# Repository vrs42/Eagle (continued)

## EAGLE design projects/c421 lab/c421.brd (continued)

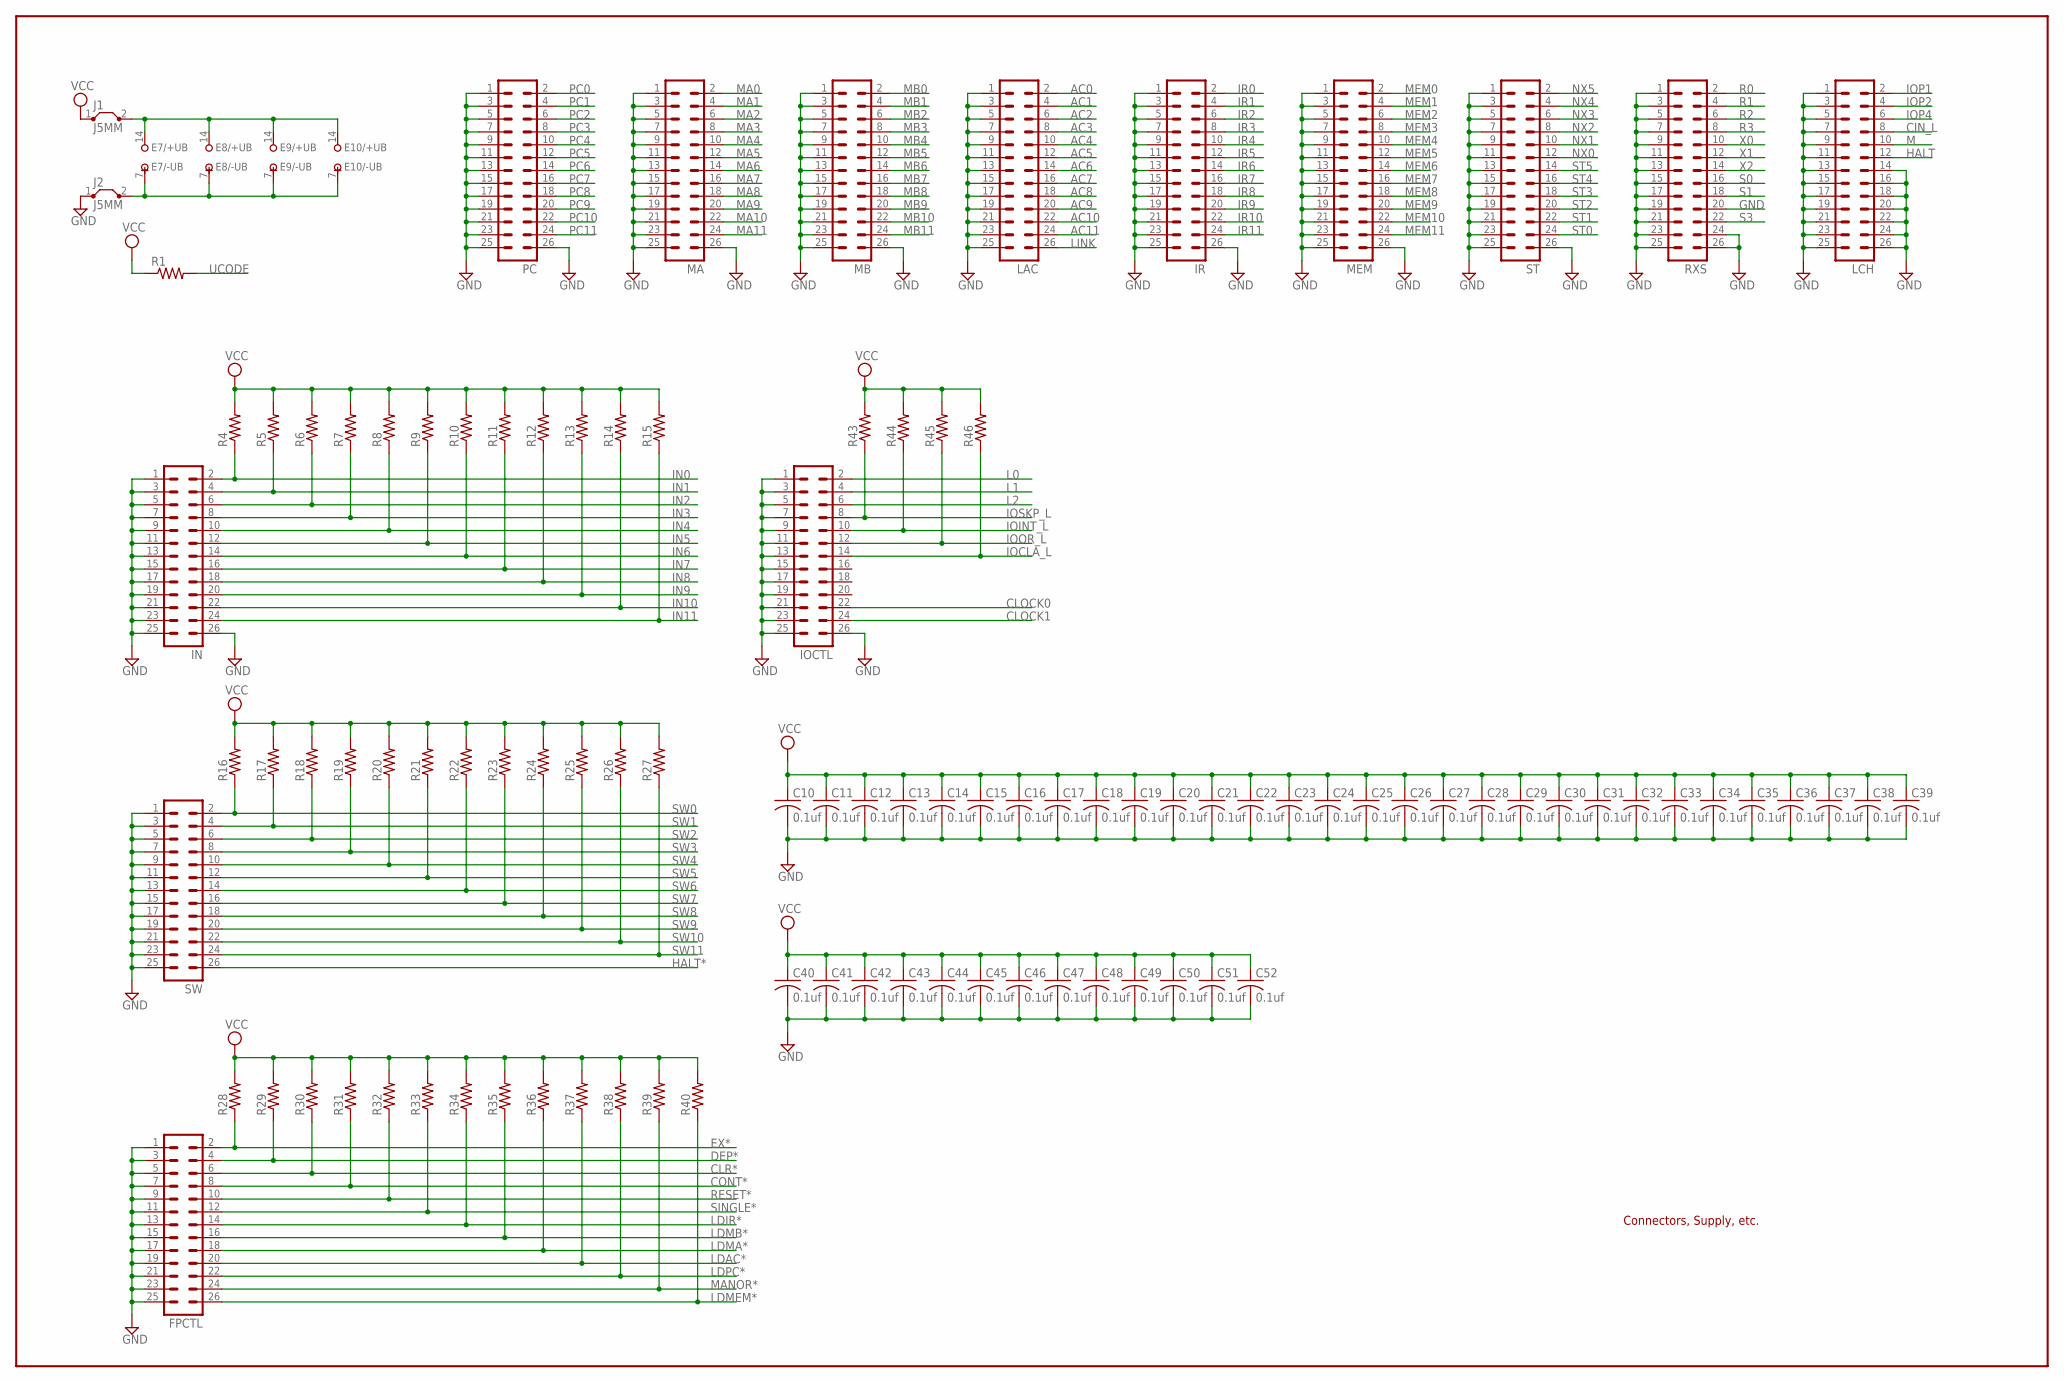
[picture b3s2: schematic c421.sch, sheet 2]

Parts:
C10, C11, C12, C13, C14, C15, C16, C17, C18, C19, C20, C21, C22, C23, C24, C25, C26, C27, C28, C29, C30, C31, C32, C33, C34, C35, C36, C37, C38, C39, C40, C41, C42, C43, C44, C45, C46, C47, C48, C49, C50, C51, C52: 0.1uf; C050-025X075
E7, E8, E9, E10: 744078N; DIL14
FPCTL: ML26
IN: ML26
IOCTL: ML26
IR: ML26
J1, J2: J5MM; 05
LAC: ML26
LCH: ML26
MA: ML26
MB: ML26
MEM: ML26
PC: ML26
R1, R4, R5, R6, R7, R8, R9, R10, R11, R12, R13, R14, R15, R16, R17, R18, R19, R20, R21, R22, R23, R24, R25, R26, R27, R28, R29, R30, R31, R32, R33, R34, R35, R36, R37, R38, R39, R40, R43, R44, R45, R46: R-US_0207/10; 0207/10
RXS: ML26
ST: ML26
SW: ML26

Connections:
+UB: E7.14 (+UB), E8.14 (+UB), E9.14 (+UB), E10.14 (+UB), J1.2
-UB: E7.7 (-UB), E8.7 (-UB), E9.7 (-UB), E10.7 (-UB), J2.2
AC0: LAC.2; also elsewhere on the board
AC1: LAC.4; also elsewhere on the board
AC2: LAC.6; also elsewhere on the board
AC3: LAC.8; also elsewhere on the board
AC4: LAC.10; also elsewhere on the board
AC5: LAC.12; also elsewhere on the board
AC6: LAC.14; also elsewhere on the board
AC7: LAC.16; also elsewhere on the board
AC8: LAC.18; also elsewhere on the board
AC9: LAC.20; also elsewhere on the board
AC10: LAC.22; also elsewhere on the board
AC11: LAC.24; also elsewhere on the board
CIN_L: LCH.8; also elsewhere on the board
CLOCK0: IOCTL.22; also elsewhere on the board
CLOCK1: IOCTL.24; also elsewhere on the board
CLR*: FPCTL.6, R30.1; also elsewhere on the board
CONT*: FPCTL.8, R31.1; also elsewhere on the board
DEP*: FPCTL.4, R29.1; also elsewhere on the board
EX*: FPCTL.2, R28.1; also elsewhere on the board
GND: C10.2, C11.2, C12.2, C13.2, C14.2, C15.2, C16.2, C17.2, C18.2, C19.2, C20.2, C21.2, C22.2, C23.2, C24.2, C25.2, C26.2, C27.2, C28.2, C29.2, C30.2, C31.2, C32.2, C33.2, C34.2, C35.2, C36.2, C37.2, C38.2, C39.2, C40.2, C41.2, C42.2, C43.2, C44.2, C45.2, C46.2, C47.2, C48.2, C49.2, C50.2, C51.2, C52.2, FPCTL.1, FPCTL.3, FPCTL.5, FPCTL.7, FPCTL.9, FPCTL.11, FPCTL.13, FPCTL.15, FPCTL.17, FPCTL.19, FPCTL.21, FPCTL.23, FPCTL.25, IN.1, IN.3, IN.5, IN.7, IN.9, IN.11, IN.13, IN.15, IN.17, IN.19, IN.21, IN.23, IN.25, IN.26, IOCTL.1, IOCTL.3, IOCTL.5, IOCTL.7, IOCTL.9, IOCTL.11, IOCTL.13, IOCTL.15, IOCTL.17, IOCTL.19, IOCTL.21, IOCTL.23, IOCTL.25, IOCTL.26, IR.1, IR.3, IR.5, IR.7, IR.9, IR.11, IR.13, IR.15, IR.17, IR.19, IR.21, IR.23, IR.25, IR.26, J2.1, LAC.1, LAC.3, LAC.5, LAC.7, LAC.9, LAC.11, LAC.13, LAC.15, LAC.17, LAC.19, LAC.21, LAC.23, LAC.25, LCH.1, LCH.3, LCH.5, LCH.7, LCH.9, LCH.11, LCH.13, LCH.14, LCH.15, LCH.16, LCH.17, LCH.18, LCH.19, LCH.20, LCH.21, LCH.22, LCH.23, LCH.24, LCH.25, LCH.26, MA.1, MA.3, MA.5, MA.7, MA.9, MA.11, MA.13, MA.15, MA.17, MA.19, MA.21, MA.23, MA.25, MA.26, MB.1, MB.3, MB.5, MB.7, MB.9, MB.11, MB.13, MB.15, MB.17, MB.19, MB.21, MB.23, MB.25, MB.26, MEM.1, MEM.3, MEM.5, MEM.7, MEM.9, MEM.11, MEM.13, MEM.15, MEM.17, MEM.19, MEM.21, MEM.23, MEM.25, MEM.26, PC.1, PC.3, PC.5, PC.7, PC.9, PC.11, PC.13, PC.15, PC.17, PC.19, PC.21, PC.23, PC.25, PC.26, RXS.1, RXS.3, RXS.5, RXS.7, RXS.9, RXS.11, RXS.13, RXS.15, RXS.17, RXS.19, RXS.20, RXS.21, RXS.23, RXS.24, RXS.25, RXS.26, ST.1, ST.3, ST.5, ST.7, ST.9, ST.11, ST.13, ST.15, ST.17, ST.19, ST.21, ST.23, ST.25, ST.26, SW.1, SW.3, SW.5, SW.7, SW.9, SW.11, SW.13, SW.15, SW.17, SW.19, SW.21, SW.23, SW.25; also elsewhere on the board
HALT: LCH.12; also elsewhere on the board
HALT*: SW.26; also elsewhere on the board
IN0: IN.2, R4.1; also elsewhere on the board
IN1: IN.4, R5.1; also elsewhere on the board
IN2: IN.6, R6.1; also elsewhere on the board
IN3: IN.8, R7.1; also elsewhere on the board
IN4: IN.10, R8.1; also elsewhere on the board
IN5: IN.12, R9.1; also elsewhere on the board
IN6: IN.14, R10.1; also elsewhere on the board
IN7: IN.16, R11.1; also elsewhere on the board
IN8: IN.18, R12.1; also elsewhere on the board
IN9: IN.20, R13.1; also elsewhere on the board
IN10: IN.22, R14.1; also elsewhere on the board
IN11: IN.24, R15.1; also elsewhere on the board
IOCLA_L: IOCTL.14, R46.1; also elsewhere on the board
IOINT_L: IOCTL.10, R44.1; also elsewhere on the board
IOOR_L: IOCTL.12, R45.1; also elsewhere on the board
IOP1: LCH.2; also elsewhere on the board
IOP2: LCH.4; also elsewhere on the board
IOP4: LCH.6; also elsewhere on the board
IOSKP_L: IOCTL.8, R43.1; also elsewhere on the board
IR0: IR.2; also elsewhere on the board
IR1: IR.4; also elsewhere on the board
IR2: IR.6; also elsewhere on the board
IR3: IR.8; also elsewhere on the board
IR4: IR.10; also elsewhere on the board
IR5: IR.12; also elsewhere on the board
IR6: IR.14; also elsewhere on the board
IR7: IR.16; also elsewhere on the board
IR8: IR.18; also elsewhere on the board
IR9: IR.20; also elsewhere on the board
IR10: IR.22; also elsewhere on the board
IR11: IR.24; also elsewhere on the board
L0: IOCTL.2; also elsewhere on the board
L1: IOCTL.4; also elsewhere on the board
L2: IOCTL.6; also elsewhere on the board
LDAC*: FPCTL.20, R37.1; also elsewhere on the board
LDIR*: FPCTL.14, R34.1; also elsewhere on the board
LDMA*: FPCTL.18, R36.1; also elsewhere on the board
LDMB*: FPCTL.16, R35.1; also elsewhere on the board
LDMEM*: FPCTL.26, R40.1; also elsewhere on the board
LDPC*: FPCTL.22, R38.1; also elsewhere on the board
LINK: LAC.26; also elsewhere on the board
M: LCH.10; also elsewhere on the board
MA0: MA.2; also elsewhere on the board
MA1: MA.4; also elsewhere on the board
MA2: MA.6; also elsewhere on the board
MA3: MA.8; also elsewhere on the board
MA4: MA.10; also elsewhere on the board
MA5: MA.12; also elsewhere on the board
MA6: MA.14; also elsewhere on the board
MA7: MA.16; also elsewhere on the board
MA8: MA.18; also elsewhere on the board
MA9: MA.20; also elsewhere on the board
MA10: MA.22; also elsewhere on the board
MA11: MA.24; also elsewhere on the board
MANOR*: FPCTL.24, R39.1; also elsewhere on the board
MB0: MB.2; also elsewhere on the board
MB1: MB.4; also elsewhere on the board
MB2: MB.6; also elsewhere on the board
MB3: MB.8; also elsewhere on the board
MB4: MB.10; also elsewhere on the board
MB5: MB.12; also elsewhere on the board
MB6: MB.14; also elsewhere on the board
MB7: MB.16; also elsewhere on the board
MB8: MB.18; also elsewhere on the board
MB9: MB.20; also elsewhere on the board
MB10: MB.22; also elsewhere on the board
MB11: MB.24; also elsewhere on the board
MEM0: MEM.2; also elsewhere on the board
MEM1: MEM.4; also elsewhere on the board
MEM2: MEM.6; also elsewhere on the board
MEM3: MEM.8; also elsewhere on the board
MEM4: MEM.10; also elsewhere on the board
MEM5: MEM.12; also elsewhere on the board
MEM6: MEM.14; also elsewhere on the board
MEM7: MEM.16; also elsewhere on the board
MEM8: MEM.18; also elsewhere on the board
MEM9: MEM.20; also elsewhere on the board
MEM10: MEM.22; also elsewhere on the board
MEM11: MEM.24; also elsewhere on the board
NX0: ST.12; also elsewhere on the board
NX1: ST.10; also elsewhere on the board
NX2: ST.8; also elsewhere on the board
NX3: ST.6; also elsewhere on the board
NX4: ST.4; also elsewhere on the board
NX5: ST.2; also elsewhere on the board
PC0: PC.2; also elsewhere on the board
PC1: PC.4; also elsewhere on the board
PC2: PC.6; also elsewhere on the board
PC3: PC.8; also elsewhere on the board
PC4: PC.10; also elsewhere on the board
PC5: PC.12; also elsewhere on the board
PC6: PC.14; also elsewhere on the board
PC7: PC.16; also elsewhere on the board
PC8: PC.18; also elsewhere on the board
PC9: PC.20; also elsewhere on the board
PC10: PC.22; also elsewhere on the board
PC11: PC.24; also elsewhere on the board
R0: RXS.2; also elsewhere on the board
R1: RXS.4; also elsewhere on the board
R2: RXS.6; also elsewhere on the board
R3: RXS.8; also elsewhere on the board
RESET*: FPCTL.10, R32.1; also elsewhere on the board
S0: RXS.16; also elsewhere on the board
S1: RXS.18; also elsewhere on the board
S3: RXS.22; also elsewhere on the board
SINGLE*: FPCTL.12, R33.1; also elsewhere on the board
ST0: ST.24; also elsewhere on the board
ST1: ST.22; also elsewhere on the board
ST2: ST.20; also elsewhere on the board
ST3: ST.18; also elsewhere on the board
ST4: ST.16; also elsewhere on the board
ST5: ST.14; also elsewhere on the board
SW0: R16.1, SW.2; also elsewhere on the board
SW1: R17.1, SW.4; also elsewhere on the board
SW2: R18.1, SW.6; also elsewhere on the board
SW3: R19.1, SW.8; also elsewhere on the board
SW4: R20.1, SW.10; also elsewhere on the board
SW5: R21.1, SW.12; also elsewhere on the board
SW6: R22.1, SW.14; also elsewhere on the board
SW7: R23.1, SW.16; also elsewhere on the board
SW8: R24.1, SW.18; also elsewhere on the board
SW9: R25.1, SW.20; also elsewhere on the board
SW10: R26.1, SW.22; also elsewhere on the board
SW11: R27.1, SW.24; also elsewhere on the board
UCODE: R1.2; also elsewhere on the board
VCC: C10.1, C11.1, C12.1, C13.1, C14.1, C15.1, C16.1, C17.1, C18.1, C19.1, C20.1, C21.1, C22.1, C23.1, C24.1, C25.1, C26.1, C27.1, C28.1, C29.1, C30.1, C31.1, C32.1, C33.1, C34.1, C35.1, C36.1, C37.1, C38.1, C39.1, C40.1, C41.1, C42.1, C43.1, C44.1, C45.1, C46.1, C47.1, C48.1, C49.1, C50.1, C51.1, C52.1, J1.1, R1.1, R4.2, R5.2, R6.2, R7.2, R8.2, R9.2, R10.2, R11.2, R12.2, R13.2, R14.2, R15.2, R16.2, R17.2, R18.2, R19.2, R20.2, R21.2, R22.2, R23.2, R24.2, R25.2, R26.2, R27.2, R28.2, R29.2, R30.2, R31.2, R32.2, R33.2, R34.2, R35.2, R36.2, R37.2, R38.2, R39.2, R40.2, R43.2, R44.2, R45.2, R46.2; also elsewhere on the board
X0: RXS.10; also elsewhere on the board
X1: RXS.12; also elsewhere on the board
X2: RXS.14; also elsewhere on the board

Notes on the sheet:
Connectors, Supply, etc.

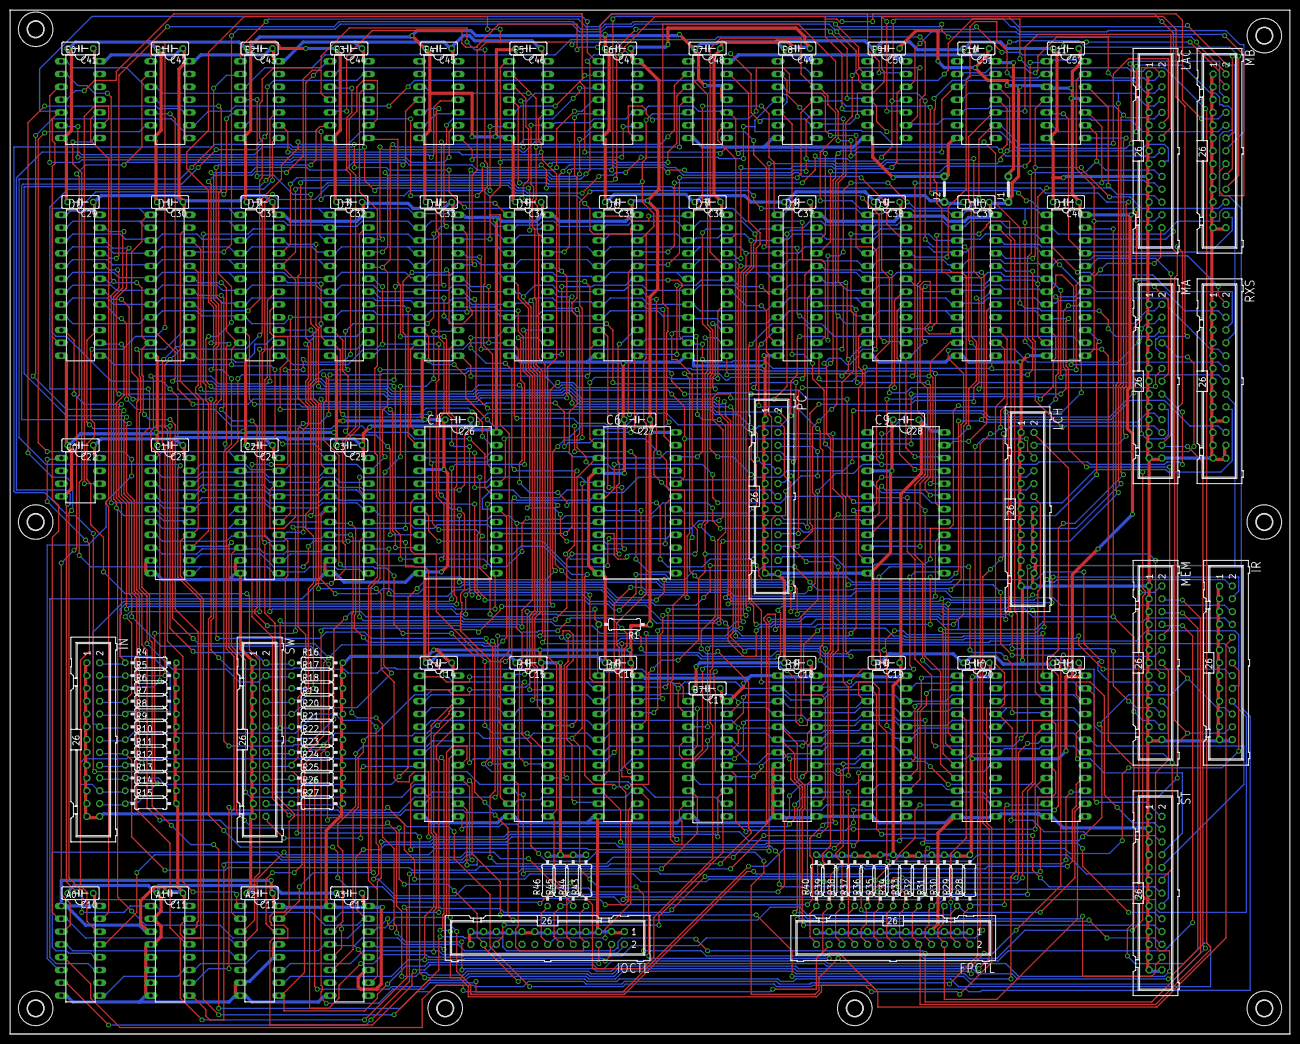
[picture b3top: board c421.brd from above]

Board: 2 copper layers, 254.0 x 203.2 mm, 151 parts (0 on the bottom side), 231 nets.

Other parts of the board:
U$1, U$2, U$3, U$4, U$5, U$6, U$7, U$8: 3,2

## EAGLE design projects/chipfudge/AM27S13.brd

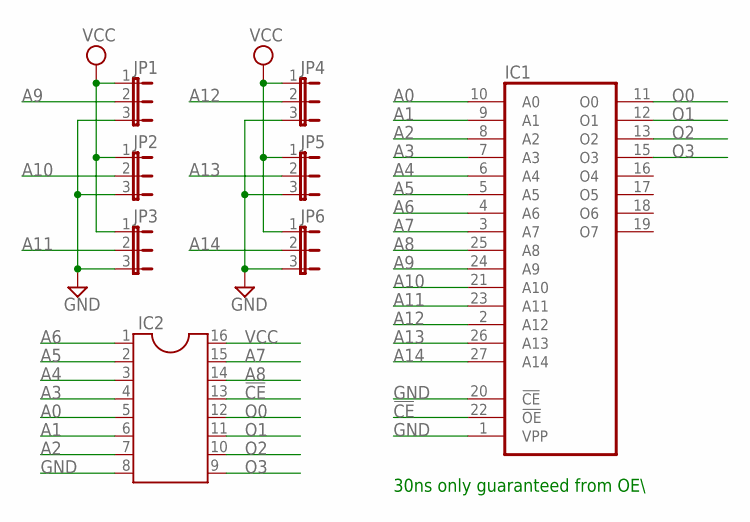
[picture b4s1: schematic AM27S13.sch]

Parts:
IC1: 27256; DIL28
IC2: DIL16
JP1, JP2, JP3, JP4, JP5, JP6: JP2E; JP2

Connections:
!CE: IC1.22 (!OE), IC2.13
A0: IC1.10 (A0), IC2.5
A1: IC1.9 (A1), IC2.6
A2: IC1.8 (A2), IC2.7
A3: IC1.7 (A3), IC2.4
A4: IC1.6 (A4), IC2.3
A5: IC1.5 (A5), IC2.2
A6: IC1.4 (A6), IC2.1
A7: IC1.3 (A7), IC2.15
A8: IC1.25 (A8), IC2.14
A9: IC1.24 (A9), JP1.2
A10: IC1.21 (A10), JP2.2
A11: IC1.23 (A11), JP3.2
A12: IC1.2 (A12), JP4.2
A13: IC1.26 (A13), JP5.2
A14: IC1.27 (A14), JP6.2
GND: IC1.1 (VPP), IC1.14 (GND), IC1.20 (!CE), IC2.8, JP1.3, JP2.3, JP3.3, JP4.3, JP5.3, JP6.3
O0: IC1.11 (O0), IC2.12
O1: IC1.12 (O1), IC2.11
O2: IC1.13 (O2), IC2.10
O3: IC1.15 (O3), IC2.9
VCC: IC1.28 (VCC), IC2.16, JP1.1, JP2.1, JP3.1, JP4.1, JP5.1, JP6.1

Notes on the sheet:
30ns only guaranteed from OE\\

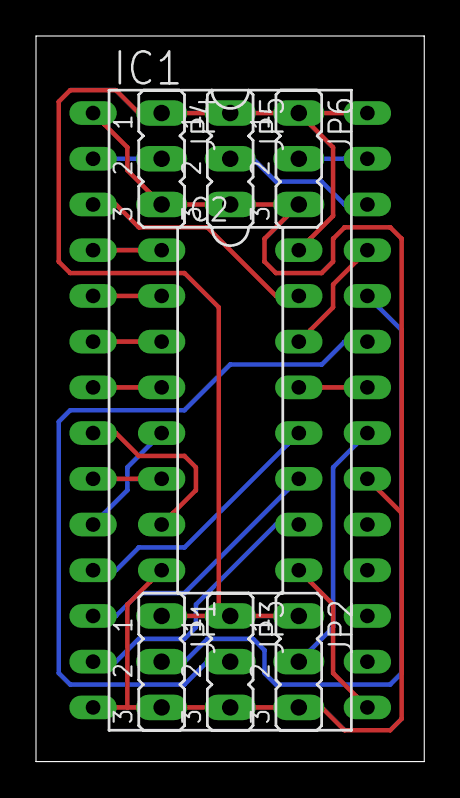
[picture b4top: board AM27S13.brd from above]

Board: 2 copper layers, 21.6 x 40.3 mm, 8 parts (0 on the bottom side), 22 nets.

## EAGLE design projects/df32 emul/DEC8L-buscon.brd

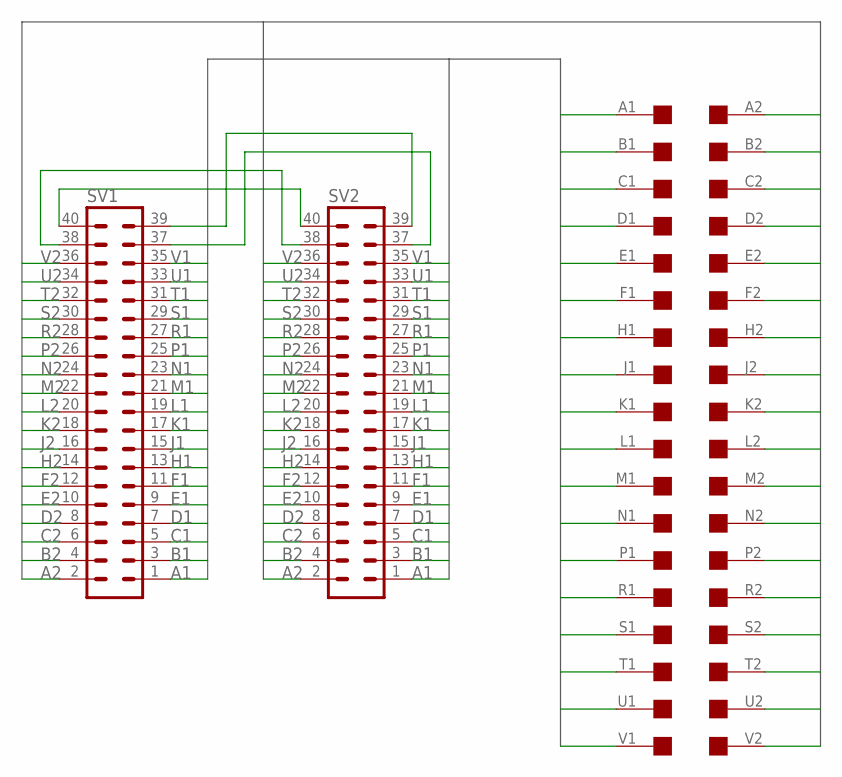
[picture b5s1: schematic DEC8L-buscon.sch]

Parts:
SV1, SV2: MA20-2W
U$1: DEC-FLIPCHIP

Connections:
A1: SV1.1, SV2.1, U$1.A1
A2: SV1.2, SV2.2, U$1.A2
B1: SV1.3, SV2.3, U$1.B1
B2: SV1.4, SV2.4, U$1.B2
C1: SV1.5, SV2.5, U$1.C1
C2: SV1.6, SV2.6, U$1.C2
D1: SV1.7, SV2.7, U$1.D1
D2: SV1.8, SV2.8, U$1.D2
E1: SV1.9, SV2.9, U$1.E1
E2: SV1.10, SV2.10, U$1.E2
F1: SV1.11, SV2.11, U$1.F1
F2: SV1.12, SV2.12, U$1.F2
H1: SV1.13, SV2.13, U$1.H1
H2: SV1.14, SV2.14, U$1.H2
J1: SV1.15, SV2.15, U$1.J1
J2: SV1.16, SV2.16, U$1.J2
K1: SV1.17, SV2.17, U$1.K1
K2: SV1.18, SV2.18, U$1.K2
L1: SV1.19, SV2.19, U$1.L1
L2: SV1.20, SV2.20, U$1.L2
M1: SV1.21, SV2.21, U$1.M1
M2: SV1.22, SV2.22, U$1.M2
N1: SV1.23, SV2.23, U$1.N1
N2: SV1.24, SV2.24, U$1.N2
unnamed: SV1.40, SV2.40
unnamed: SV1.38, SV2.38
unnamed: SV1.37, SV2.37
unnamed: SV1.39, SV2.39
P1: SV1.25, SV2.25, U$1.P1
P2: SV1.26, SV2.26, U$1.P2
R1: SV1.27, SV2.27, U$1.R1
R2: SV1.28, SV2.28, U$1.R2
S1: SV1.29, SV2.29, U$1.S1
S2: SV1.30, SV2.30, U$1.S2
T1: SV1.31, SV2.31, U$1.T1
T2: SV1.32, SV2.32, U$1.T2
U1: SV1.33, SV2.33, U$1.U1
U2: SV1.34, SV2.34, U$1.U2
V1: SV1.35, SV2.35, U$1.V1
V2: SV1.36, SV2.36, U$1.V2

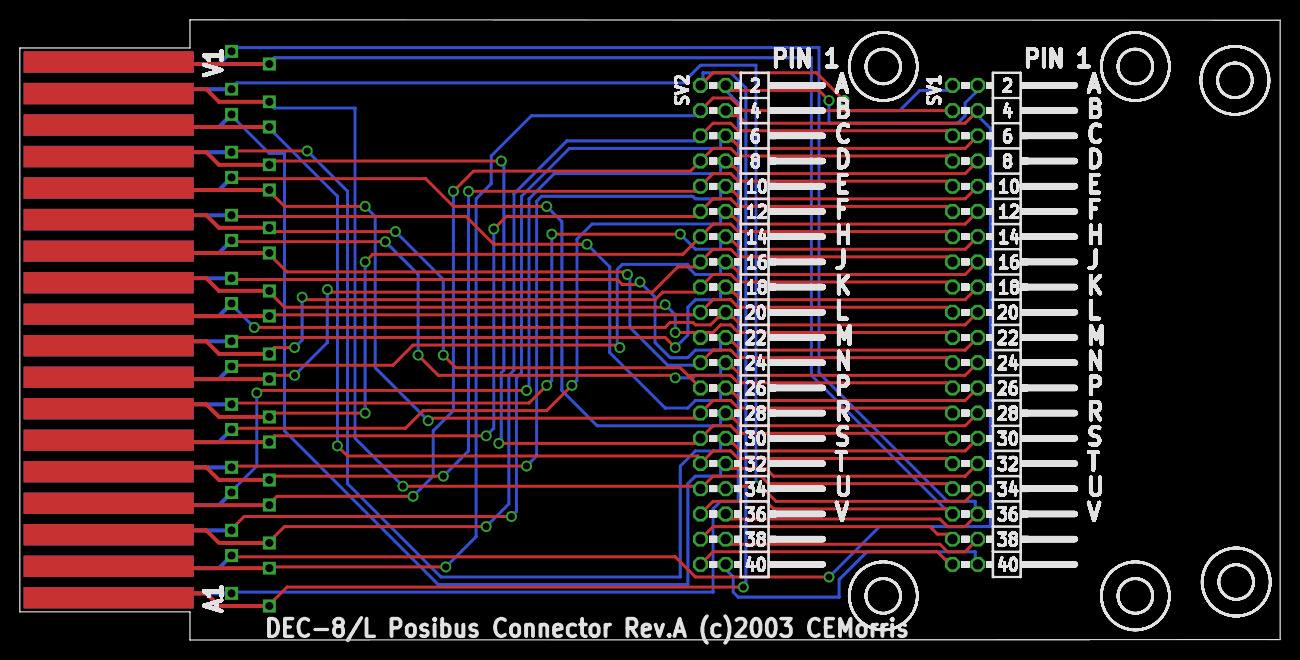
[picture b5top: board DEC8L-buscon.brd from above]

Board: 2 copper layers, 127.0 x 62.5 mm, 9 parts (0 on the bottom side), 40 nets.

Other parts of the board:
U$2, U$3, U$4, U$5, U$6, U$7: 3,3
